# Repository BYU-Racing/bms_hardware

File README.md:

# BYU Racing 2027 BMS Project

This repo contains all relevant PCB files and explanations relating to the team's custom solution for a Battery Management System (BMS)

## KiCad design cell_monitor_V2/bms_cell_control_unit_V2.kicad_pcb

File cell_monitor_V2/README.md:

# BMS Cell Monitor V2 Files
This folder contains the KiCad project files for the BMS Cell Monitor V2.

PCB handoff from Rugby 11/10/2026 ☠️🌹⛓️

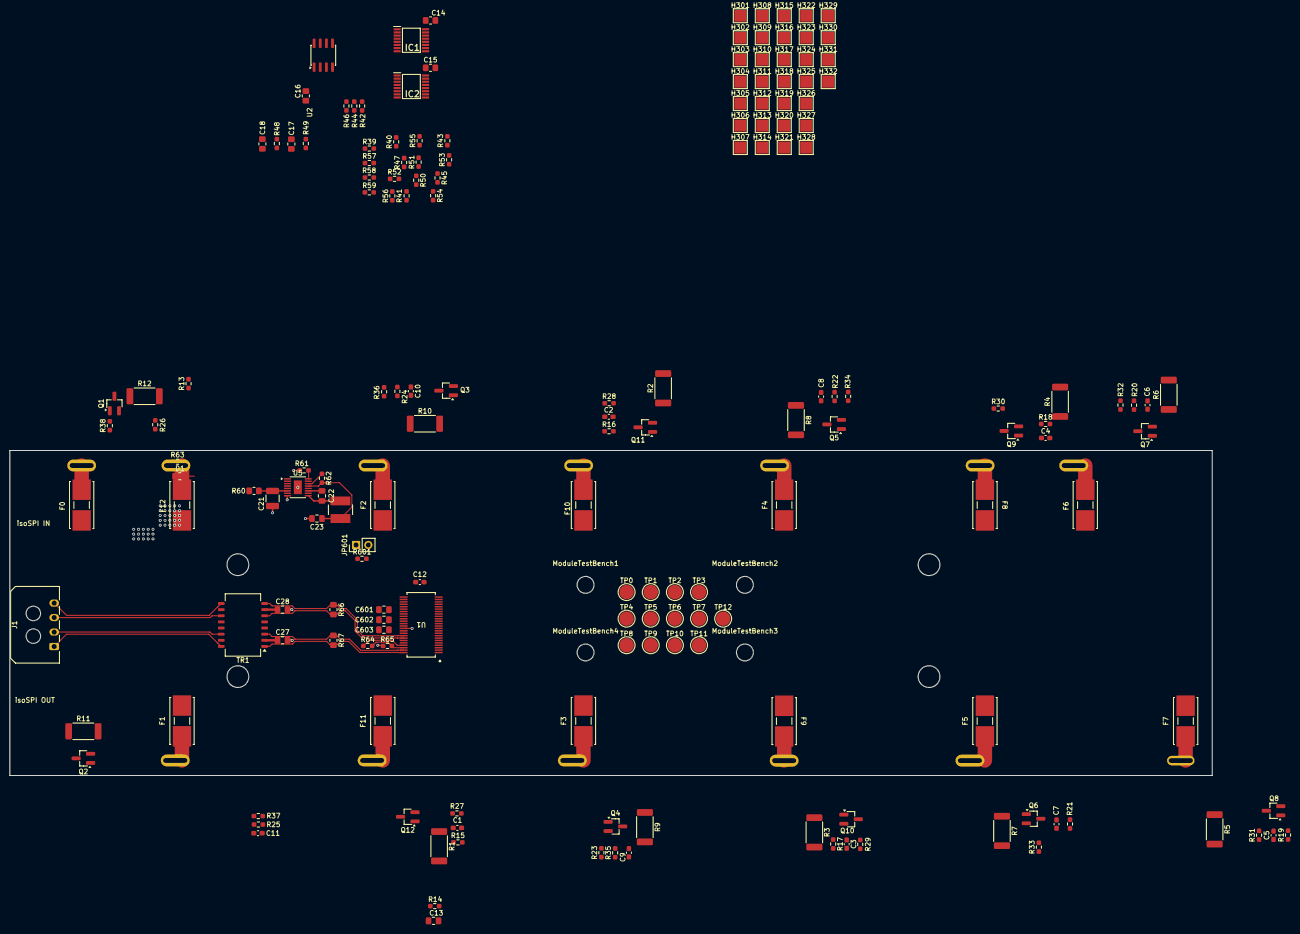
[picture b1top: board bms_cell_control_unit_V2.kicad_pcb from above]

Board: 4 copper layers, 249.0 x 67.3 mm, 199 parts (0 on the bottom side), 124 nets.

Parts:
C1, C2, C3, C4, C5, C6, C7, C8, C9, C10, C11, C12: 10nF; C_0603_1608Metric_Pad1.08x0.95mm_HandSolder
C13: 100nF; C_0805_2012Metric_Pad1.18x1.45mm_HandSolder
C14: 1uF; R_0805_2012Metric_Pad1.20x1.40mm_HandSolder
C15, C16: 1uf; R_0805_2012Metric_Pad1.20x1.40mm_HandSolder
C17, C18: 10nF; R_0805_2012Metric_Pad1.20x1.40mm_HandSolder
C21: 2.2uF; C_1210_3225Metric_Pad1.33x2.70mm_HandSolder
C22, C23: 22uF; C_0805_2012Metric_Pad1.18x1.45mm_HandSolder
C27, C28: 10nF; C_0805_2012Metric_Pad1.18x1.45mm_HandSolder
C601, C602, C603: 1uF; C_0805_2012Metric_Pad1.18x1.45mm_HandSolder
D1: LED; R_0805_2012Metric_Pad1.20x1.40mm_HandSolder
F0, F12: 500mA; Littelfuse_01550900M_Fuse_Blok_Cartridge
F1, F2, F3, F4, F5, F6, F7, F8, F9, F10, F11: 250mA; Littelfuse_01550900M_Fuse_Blok_Cartridge
H0, H1, H2, H3, H4, H5, H6, H7, H8, H9, H10, H11, H12: Old Voltage Tap; voltage_tap
H13, H14, H14#2, H14#3, H14#4, H14#5, H15, H16: MountingScrew; MountingHole_4mm
H301: TH1+; TestPoint_Pad_2.5x2.5mm
H302: TH2+; TestPoint_Pad_2.5x2.5mm
H303: TH1-; TestPoint_Pad_2.5x2.5mm
H304: TH2-; TestPoint_Pad_2.5x2.5mm
H305: TH3+; TestPoint_Pad_2.5x2.5mm
H306: TH4+; TestPoint_Pad_2.5x2.5mm
H307: TH4-; TestPoint_Pad_2.5x2.5mm
H308: TH3-; TestPoint_Pad_2.5x2.5mm
H309: TH5+; TestPoint_Pad_2.5x2.5mm
H310: TH6+; TestPoint_Pad_2.5x2.5mm
H311: TH6-; TestPoint_Pad_2.5x2.5mm
H312: TH5-; TestPoint_Pad_2.5x2.5mm
H313: TH7+; TestPoint_Pad_2.5x2.5mm
H314: TH8+; TestPoint_Pad_2.5x2.5mm
H315: TH8-; TestPoint_Pad_2.5x2.5mm
H316: TH7-; TestPoint_Pad_2.5x2.5mm
H317: TH9+; TestPoint_Pad_2.5x2.5mm
H318: TH10+; TestPoint_Pad_2.5x2.5mm
H319: TH10-; TestPoint_Pad_2.5x2.5mm
H320: TH9-; TestPoint_Pad_2.5x2.5mm
H321: TH11+; TestPoint_Pad_2.5x2.5mm
H322: TH12+; TestPoint_Pad_2.5x2.5mm
H323: TH12-; TestPoint_Pad_2.5x2.5mm
H324: TH11-; TestPoint_Pad_2.5x2.5mm
H325: TH13+; TestPoint_Pad_2.5x2.5mm
H326: TH14+; TestPoint_Pad_2.5x2.5mm
H327: TH15+; TestPoint_Pad_2.5x2.5mm
H328: TH16+; TestPoint_Pad_2.5x2.5mm
H329: TH14-; TestPoint_Pad_2.5x2.5mm
H330: TH16-; TestPoint_Pad_2.5x2.5mm
H331: TH13-; TestPoint_Pad_2.5x2.5mm
H332: TH15-; TestPoint_Pad_2.5x2.5mm
IC1, IC2: TMUX1308AQPWRQ1; SOP65P640X120-16N
J1: isoSPI Daisy Chain IN; Molex_Micro-Fit_3.0_43650-0400_1x04_P3.00mm_Horizontal
JP601: Current Jumper; PinHeader_1x02_P2.54mm_Vertical
L1: 33uH; IND_LQH5BPH330MT0L
ModuleTestBench1, ModuleTestBench2, ModuleTestBench3, ModuleTestBench4: MountingHole; MountingHole_3.5mm
Q1, Q2, Q3, Q4, Q5, Q6, Q7, Q8, Q9, Q10, Q11, Q12: BSS308PE; SOT-23_Handsoldering
R1, R2, R3, R4, R5, R6, R7, R8, R9, R10, R11, R12: 33; R_2512_6332Metric_Pad1.40x3.35mm_HandSolder
R13, R14, R15, R16, R17, R18, R19, R20, R21, R22, R23, R24, R25, R26, R48, R49: 100; R_0603_1608Metric_Pad0.98x0.95mm_HandSolder
R27, R28, R29, R30, R31, R32, R33, R34, R35, R36, R37, R38: 3.3k; R_0603_1608Metric_Pad0.98x0.95mm_HandSolder
R39, R40, R41, R43, R45, R47, R50, R51, R52, R53, R54, R55, R56, R57, R58, R59: 10k; R_0603_1608Metric_Pad0.98x0.95mm_HandSolder
R42, R44, R46: 4.7K; R_0603_1608Metric_Pad0.98x0.95mm_HandSolder
R60: 470; R_0805_2012Metric_Pad1.20x1.40mm_HandSolder
R61: 374k; R_0603_1608Metric_Pad0.98x0.95mm_HandSolder
R62: 220k; R_0603_1608Metric_Pad0.98x0.95mm_HandSolder
R63: 2.2k; R_0603_1608Metric_Pad0.98x0.95mm_HandSolder
R64, R65: 1k; R_0603_1608Metric_Pad0.98x0.95mm_HandSolder
R66, R67: 100; R_0805_2012Metric_Pad1.20x1.40mm_HandSolder
R601: 0; R_0603_1608Metric_Pad0.98x0.95mm_HandSolder
TP0, TP1, TP2, TP3, TP4, TP5, TP6, TP7, TP8, TP9, TP10, TP11, TP12: TestPoint; TestPoint_Pad_D3.0mm
TR1: TG110I-AE050N5xx; Transformer_Ethernet_Halo_N5_SO-16_7.11x12.7mm
U1: LTC6811HGI-1I-3ZZTRPBF; 05-08-1887_ADI
U2: TLV9002IDR; SOIC-8_3.9x4.9mm_P1.27mm
U5: LT3990HMSEI-5I-PBF; MSOP-16-1EP_3x4.039mm_P0.5mm_EP1.651x2.845mm

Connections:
/Power Rail/DRIVE: U1.38 (DRIVE), U5.4 (EN/UVLO)
/Power Rail/VREG: C14.1, C15.1, C16.1, C603.1, IC1.16 (VDD), IC2.16 (VDD), JP601.2 (B), R42.1, R44.1, R46.1, R63.2, R601.2, U1.37 (VREG), U1.40 (ISOMD), U2.8 (V+)
/Power Rail/V_REF1: C602.1, U1.35 (VREF1)
/Power Rail/V_REF2: C601.1, R39.1, R40.1, R41.1, R43.1, R45.1, R47.1, R50.1, R51.1, R52.1, R53.1, R54.1, R55.1, R56.1, R57.1, R58.1, R59.1, U1.34 (VREF2)
/Power Rail/V_full_stack_fused: F12.2, Q12.2 (S), R14.2, R15.2, R60.2, TP12.1 (1_1)
/Temperature Sensing/GPIO1(MUX_OUT_1): C18.1, R48.1, U1.27 (GPIO1)
/Temperature Sensing/GPIO2(MUX_OUT_2): C17.1, R49.1, U1.28 (GPIO2)
/Temperature Sensing/GPIO3: IC1.11 (A0), IC2.11 (A0), R42.2, U1.29 (GPIO3)
/Temperature Sensing/GPIO4: IC1.10 (A1), IC2.10 (A1), R44.2, U1.32 (GPIO4)
/Temperature Sensing/GPIO5: IC1.9 (A2), IC2.9 (A2), R46.2, U1.33 (GPIO5)
/Temperature Sensing/MUX1_OUT: IC1.3 (D), U2.3
/Temperature Sensing/MUX2_OUT: IC2.3 (D), U2.5
/Temperature Sensing/TH1: H301.1 (1_1), IC1.13 (S0), R39.2
/Temperature Sensing/TH2: H302.1 (1_1), IC1.14 (S1), R40.2
/Temperature Sensing/TH3: H305.1 (1_1), IC1.15 (S2), R41.2
/Temperature Sensing/TH4: H306.1 (1_1), IC1.12 (S3), R43.2
/Temperature Sensing/TH5: H309.1 (1_1), IC1.1 (S4), R45.2
/Temperature Sensing/TH6: H310.1 (1_1), IC1.5 (S5), R47.2
/Temperature Sensing/TH7: H313.1 (1_1), IC1.2 (S6), R50.2
/Temperature Sensing/TH8: H314.1 (1_1), IC1.4 (S7), R51.2
/Temperature Sensing/TH9: H317.1 (1_1), IC2.13 (S0), R52.2
/Temperature Sensing/TH10: H318.1 (1_1), IC2.14 (S1), R53.2
/Temperature Sensing/TH11: H321.1 (1_1), IC2.15 (S2), R54.2
/Temperature Sensing/TH12: H322.1 (1_1), IC2.12 (S3), R55.2
/Temperature Sensing/TH13: H325.1 (1_1), IC2.1 (S4), R56.2
/Temperature Sensing/TH14: H326.1 (1_1), IC2.5 (S5), R57.2
/Temperature Sensing/TH15: H327.1 (1_1), IC2.2 (S6), R58.2
/Temperature Sensing/TH16: H328.1 (1_1), IC2.4 (S7), R59.2
/Voltage Sense Leads/C0: C12.2, R13.1, U1.26 (C0)
/Voltage Sense Leads/C1: C11.2, C12.1, R26.1, U1.24 (C1)
/Voltage Sense Leads/C2: C10.2, C11.1, R25.1, U1.22 (C2)
/Voltage Sense Leads/C3: C9.2, C10.1, R24.1, U1.20 (C3)
/Voltage Sense Leads/C4: C8.2, C9.1, R23.1, U1.18 (C4)
/Voltage Sense Leads/C5: C7.2, C8.1, R22.1, U1.16 (C5)
/Voltage Sense Leads/C6: C6.2, C7.1, R21.1, U1.14 (C6)
/Voltage Sense Leads/C7: C5.2, C6.1, R20.1, U1.12 (C7)
/Voltage Sense Leads/C8: C4.2, C5.1, R19.1, U1.10 (C8)
/Voltage Sense Leads/C9: C3.2, C4.1, R18.1, U1.8 (C9)
/Voltage Sense Leads/C10: C2.2, C3.1, R17.1, U1.6 (C10)
/Voltage Sense Leads/C11: C1.2, C2.1, R16.1, U1.4 (C11)
/Voltage Sense Leads/C12: C1.1, R15.1, U1.2 (C12)
/Voltage Sense Leads/S1: R38.1, U1.25 (S1)
/Voltage Sense Leads/S2: R37.1, U1.23 (S2)
/Voltage Sense Leads/S3: R36.1, U1.21 (S3)
/Voltage Sense Leads/S4: R35.1, U1.19 (S4)
/Voltage Sense Leads/S5: R34.1, U1.17 (S5)
/Voltage Sense Leads/S6: R33.1, U1.15 (S6)
/Voltage Sense Leads/S7: R32.1, U1.13 (S7)
/Voltage Sense Leads/S8: R31.1, U1.11 (S8)
/Voltage Sense Leads/S9: R30.1, U1.9 (S9)
/Voltage Sense Leads/S10: R29.1, U1.7 (S10)
/Voltage Sense Leads/S11: R28.1, U1.5 (S11)
/Voltage Sense Leads/S12: R27.1, U1.3 (S12)
/Voltage Sense Leads/VBUS1: F1.1, H1.1 (1_1)
/Voltage Sense Leads/VBUS2: F2.1, H2.1 (1_1)
/Voltage Sense Leads/VBUS3: F3.1, H3.1 (1_1)
/Voltage Sense Leads/VBUS4: F4.1, H4.1 (1_1)
/Voltage Sense Leads/VBUS5: F5.1, H5.1 (1_1)
/Voltage Sense Leads/VBUS6: F6.1, H6.1 (1_1)
/Voltage Sense Leads/VBUS7: F7.1, H7.1 (1_1)
/Voltage Sense Leads/VBUS8: F8.1, H8.1 (1_1)
/Voltage Sense Leads/VBUS9: F9.1, H9.1 (1_1)
/Voltage Sense Leads/VBUS10: F10.1, H10.1 (1_1)
/Voltage Sense Leads/VBUS11: F11.1, H11.1 (1_1)
/Voltage Sense Leads/VBUS12: F12.1, H12.1 (1_1)
/Voltage Sense Leads/VBUS_GNDREF: F0.1, H0.1 (1_1)
/Voltage Sense Leads/VI+: C13.1, R14.1, U1.1 (V+)
/isoSPI Daisy Chain/+: R66.2, TR1.6 (RX-), U1.42 (SCK(IPA))
/isoSPI Daisy Chain/-: R66.1, TR1.8 (RX+), U1.41 (CSB(IMA))
/isoSPI Daisy Chain/I+: R67.2, TR1.1 (TX-), U1.48 (IPB)
/isoSPI Daisy Chain/I-: R67.1, TR1.3 (TX+), U1.47 (IMB)
/isoSPI Daisy Chain/IBIAS: R64.2, U1.45 (IBIAS)
/isoSPI Daisy Chain/ICMP: R64.1, R65.2, U1.46 (ICMP)
/isoSPI Daisy Chain/isoSPIAI+: J1.3, TR1.11 (RD-)
/isoSPI Daisy Chain/isoSPIAI-: J1.4, TR1.9 (RD+)
/isoSPI Daisy Chain/isoSPIBI+: J1.1, TR1.16 (TD-)
/isoSPI Daisy Chain/isoSPIBI-: J1.2, TR1.14 (TD+)
GNDREF: C13.2, C14.2, C15.2, C16.2, C17.2, C18.2, C21.2, C23.2, C27.2, C28.2, C601.2, C602.2, C603.2, D1.1 (K), F0.2, H303.1 (1_1), H304.1 (1_1), H307.1 (1_1), H308.1 (1_1), H311.1 (1_1), H312.1 (1_1), H315.1 (1_1), H316.1 (1_1), H319.1 (1_1), H320.1 (1_1), H323.1 (1_1), H324.1 (1_1), H329.1 (1_1), H330.1 (1_1), H331.1 (1_1), H332.1 (1_1), IC1.6 (~EN), IC1.8 (GND), IC2.6 (~EN), IC2.8 (GND), R12.2, R13.2, R61.2, R65.1, TP0.1 (1_1), U1.30 (V-), U1.31 (V-), U1.36 (DTEN), U2.4 (V-), U5.8 (GND), U5.17 (EPAD)
unnamed: D1.2 (A), R63.1
unnamed: C23.1, JP601.1 (A), L1.2, R62.1, R601.1, U5.1 (FB/VOUT), U5.2 (FB/VOUT), U5.13 (BD)
unnamed: Q1.3 (D), R12.1
unnamed: Q1.1 (G), R38.2
unnamed: F1.2, Q1.2 (S), R11.2, R26.2, TP1.1 (1_1)
unnamed: Q2.3 (D), R11.1
unnamed: Q2.1 (G), R37.2
unnamed: F2.2, Q2.2 (S), R10.2, R25.2, TP2.1 (1_1)
unnamed: Q3.3 (D), R10.1
unnamed: Q3.1 (G), R36.2
unnamed: F3.2, Q3.2 (S), R9.2, R24.2, TP3.1 (1_1)
unnamed: Q4.3 (D), R9.1
unnamed: Q4.1 (G), R35.2
unnamed: F4.2, Q4.2 (S), R8.2, R23.2, TP4.1 (1_1)
unnamed: Q5.3 (D), R8.1
unnamed: Q5.1 (G), R34.2
unnamed: F5.2, Q5.2 (S), R7.2, R22.2, TP5.1 (1_1)
unnamed: Q6.3 (D), R7.1
unnamed: Q6.1 (G), R33.2
unnamed: F6.2, Q6.2 (S), R6.2, R21.2, TP6.1 (1_1)
unnamed: Q7.3 (D), R6.1
unnamed: Q7.1 (G), R32.2
unnamed: F7.2, Q7.2 (S), R5.2, R20.2, TP7.1 (1_1)
unnamed: Q8.3 (D), R5.1
unnamed: Q8.1 (G), R31.2
unnamed: F8.2, Q8.2 (S), R4.2, R19.2, TP8.1 (1_1)
unnamed: Q9.3 (D), R4.1
unnamed: Q9.1 (G), R30.2
unnamed: F9.2, Q9.2 (S), R3.2, R18.2, TP9.1 (1_1)
unnamed: Q10.3 (D), R3.1
unnamed: Q10.1 (G), R29.2
unnamed: F10.2, Q10.2 (S), R2.2, R17.2, TP10.1 (1_1)
unnamed: Q11.3 (D), R2.1
unnamed: Q11.1 (G), R28.2
unnamed: F11.2, Q11.2 (S), R1.2, R16.2, TP11.1 (1_1)
unnamed: Q12.3 (D), R1.1
unnamed: Q12.1 (G), R27.2
unnamed: R48.2, U2.1, U2.2
unnamed: R49.2, U2.6, U2.7
unnamed: C28.1, TR1.7 (C_RX)
unnamed: C27.1, TR1.2 (C_TX)
unnamed: C22.1, U5.11 (BOOST)
unnamed: R62.2, U5.14 (PG)
unnamed: R61.1, U5.16 (RT)
unnamed: C22.2, L1.1, U5.9 (SW)
unnamed: C21.1, R60.1, U5.6 (VIN)

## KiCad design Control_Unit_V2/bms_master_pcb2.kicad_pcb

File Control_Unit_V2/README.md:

# BMS Control Unit V2 Files
This folder contains the KiCad project files for the BMS Control Unit V2.

PCB handoff from Rugby 11/10/2026 ☠️🌹⛓️

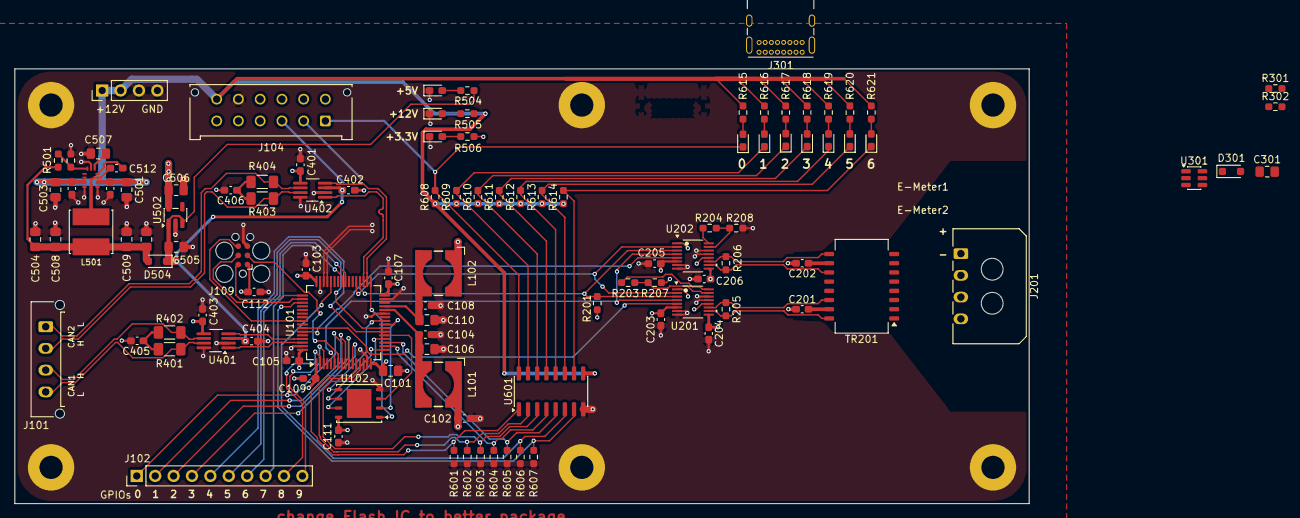
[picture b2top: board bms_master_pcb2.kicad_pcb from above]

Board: 4 copper layers, 140.0 x 60.0 mm, 115 parts (0 on the bottom side), 91 nets.

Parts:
C101: 4.7u; C_0805_2012Metric_Pad1.18x1.45mm_HandSolder
C102, C103, C104, C105, C107, C108, C109, C111, C112, C203, C204, C205, C206, C401, C402, C403, C404: 100n; C_0603_1608Metric_Pad1.08x0.95mm_HandSolder
C106, C110, C505, C506, C507: 1u; C_0805_2012Metric_Pad1.18x1.45mm_HandSolder
C201, C202: 27p; C_0603_1608Metric_Pad1.08x0.95mm_HandSolder
C301, C501, C503: 10u; C_0805_2012Metric_Pad1.18x1.45mm_HandSolder
C405, C406: 240p; C_0603_1608Metric_Pad1.08x0.95mm_HandSolder
C502, C504, C508, C509: 22u; C_0805_2012Metric_Pad1.18x1.45mm_HandSolder
C510, C511: 220n; C_0603_1608Metric_Pad1.08x0.95mm_HandSolder
C512: 0.1u; C_0603_1608Metric_Pad1.08x0.95mm_HandSolder
D301, D504: 1N4448WS; D_SOD-323_HandSoldering
D501: 5V LED; LED_0603_1608Metric_Pad1.05x0.95mm_HandSolder
D502: 12V LED; LED_0603_1608Metric_Pad1.05x0.95mm_HandSolder
D503: 3.3V LED; LED_0603_1608Metric_Pad1.05x0.95mm_HandSolder
D601, D602, D603, D604, D605, D606, D607: LED_Small; LED_0603_1608Metric_Pad1.05x0.95mm_HandSolder
H101, H102, H103, H104, H105, H106: MountingHole; MountingHole_3.2mm_M3_Pad
J101: CAN Connector; Molex_Micro-Fit_3.0_43650-0415_1x04_P3.00mm_Vertical
J102: GPIO; PinHeader_1x10_P2.54mm_Vertical
J103: EXTRA POWER IN; PinHeader_1x04_P2.54mm_Vertical
J104: Connector to GLV plug; Molex_Micro-Fit_3.0_43045-1212_2x06_P3.00mm_Vertical
J109: TC2030; Tag-Connect_TC2030-IDC-FP_2x03_P1.27mm_Vertical
J201: isoSPI Daisy Chain; Molex_Micro-Fit_3.0_43650-0400_1x04_P3.00mm_Horizontal
J301: USB4085-GF-A; USB_C_Receptacle_GCT_USB4085
L101, L102: 100u; WE-HEPC_6030
L501: 10u; IND_SRN6045TA-2R2Y
R201: 2K; R_0603_1608Metric_Pad0.98x0.95mm_HandSolder
R203, R204, R207, R208, R506: 1k; R_0603_1608Metric_Pad0.98x0.95mm_HandSolder
R205, R206: 100; R_0603_1608Metric_Pad0.98x0.95mm_HandSolder
R301, R302: 5.1K; R_0603_1608Metric_Pad0.98x0.95mm_HandSolder
R401, R402, R403, R404: 60; R_1206_3216Metric_Pad1.30x1.75mm_HandSolder
R501: 100k; R_0603_1608Metric_Pad0.98x0.95mm_HandSolder
R502: 24.9k; R_0603_1608Metric_Pad0.98x0.95mm_HandSolder
R504: 2.2k; R_0603_1608Metric_Pad0.98x0.95mm_HandSolder
R505, R615, R616, R617, R618, R619, R620, R621: 4.7k; R_0603_1608Metric_Pad0.98x0.95mm_HandSolder
R601, R602, R603, R604, R605, R606, R607, R608, R609, R610, R611, R612, R613, R614: 10K; R_0603_1608Metric_Pad0.98x0.95mm_HandSolder
TR201: TG110-E050N5xx; Transformer_Ethernet_Halo_N5_SO-16_7.11x12.7mm
U101: STM32G474RETx; LQFP-64_10x10mm_P0.5mm
U102: SST26VF064B-104V/MF; WDFN-8-1EP_6x5mm_P1.27mm_EP3.4x4mm
U201, U202: LTC6820HMS-TRPBF; MS_05-08-1669_ADI
U301: USBLC6-2SC6; SOT-23-6
U401, U402: TCAN1044AVDDFRQ1; TSOT-23-8_HandSoldering
U502: AP2112K-3.3; SOT-23-5
U503: LMR33620CQ5RNXRQ1; RNX0012B
U601: TPL7407LAD; SOIC-16_3.9x9.9mm_P1.27mm

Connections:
+3.3V: C101.1, C102.1, C103.1, C105.1, C107.1, C109.1, C111.1, C112.1, C203.1, C204.1, C205.1, C206.1, C401.1, C403.1, C506.1, J109.1, L101.1, L102.1, R201.2, R506.1, U101.1 (VBAT), U101.16 (VDD), U101.32 (VDD), U101.48 (VDD), U101.64 (VDD), U102.8 (VCC), U201.1 (EN), U201.6 (VDDS), U201.9 (VDD), U201.12 (MSTR), U202.1 (EN), U202.6 (VDDS), U202.9 (VDD), U202.12 (MSTR), U401.5 (VIO), U402.5 (VIO), U502.5 (VOUT)
+5V: C301.1, C402.1, C404.1, C505.1, D301.1 (K), D504.1 (K), R504.1, U301.5 (VBUS), U401.3 (VCC), U402.3 (VCC), U502.1 (VIN), U502.3 (EN)
+12V: C501.1, C503.1, C510.2, C511.2, J103.1, J103.2, J104.12, R505.1, R608.1, R609.1, R610.1, R611.1, R612.1, R613.1, R614.1, R615.1, R616.1, R617.1, R618.1, R619.1, R620.1, R621.1, U503.2 (VIN), U503.9 (EN), U503.10 (VIN), U601.9 (COM)
/BMS SD STATUS: D601.1 (K), J104.1, R608.2, U601.16 (OUT1)
/CAN1_N: U101.62 (FDCAN1_TX), U401.1 (TXD)
/CAN1_P: U101.61 (FDCAN1_RX), U401.4 (RXD)
/CAN2_N: U101.35 (FDCAN2_TX), U402.1 (TXD)
/CAN2_P: U101.34 (FDCAN2_RX), U402.4 (RXD)
/CAN/CAN.1+: J101.4, R401.1, U401.7 (CANH)
/CAN/CAN.1-: J101.3, R402.1, U401.6 (CANL)
/CAN/CAN.2+: J101.2, R403.1, U402.7 (CANH)
/CAN/CAN.2-: J101.1, R404.1, U402.6 (CANL)
/DIG_OUT_0: R601.1, U101.12 (PA0), U601.1 (IN1)
/DIG_OUT_1: R602.1, U101.13 (PA1), U601.2 (IN2)
/DIG_OUT_2: R603.1, U101.14 (PA2), U601.3 (IN3)
/DIG_OUT_3: R604.1, U101.18 (PA4), U601.4 (IN4)
/DIG_OUT_4: R605.1, U101.19 (PA5), U601.5 (IN5)
/DIG_OUT_5: R606.1, U101.44 (PA10), U601.6 (IN6)
/DIG_OUT_6: R607.1, U101.51 (PA15), U601.7 (IN7)
/Digital Outputs and Happy Lights/BMS_OUT_1: D602.1 (K), R609.2, U601.15 (OUT2)
/Digital Outputs and Happy Lights/BMS_OUT_2: D603.1 (K), R610.2, U601.14 (OUT3)
/Digital Outputs and Happy Lights/BMS_OUT_3: D604.1 (K), R611.2, U601.13 (OUT4)
/Digital Outputs and Happy Lights/BMS_OUT_4: D605.1 (K), R612.2, U601.12 (OUT5)
/Digital Outputs and Happy Lights/BMS_OUT_5: D606.1 (K), R613.2, U601.11 (OUT6)
/Digital Outputs and Happy Lights/BMS_OUT_6: D607.1 (K), R614.2, U601.10 (OUT7)
/GPIO_0: J102.1, U101.8 (PC0)
/GPIO_1: J102.2, U101.9 (PC1)
/GPIO_2: J102.3, U101.10 (PC2)
/GPIO_3: J102.4, U101.11 (PC3)
/GPIO_4: J102.5, U101.22 (PC4)
/GPIO_5: J102.6, U101.23 (PC5)
/GPIO_6: J102.7, U101.40 (PC8)
/GPIO_7: J102.8, U101.41 (PC9)
/GPIO_8: J102.9, U101.2 (PC13)
/GPIO_9: J102.10, U101.3 (PC14)
/QSPI.CLK: U101.17 (QUADSPI1_CLK), U102.6 (SCK)
/QSPI.IO0: U101.25 (QUADSPI1_BK1_IO0), U102.5 (IO0)
/QSPI.IO1: U101.24 (QUADSPI1_BK1_IO1), U102.2 (IO1)
/QSPI.IO2: U101.21 (QUADSPI1_BK1_IO2), U102.3 (IO2)
/QSPI.IO3: U101.20 (QUADSPI1_BK1_IO3), U102.7 (IO3)
/QSPI.NCS: U101.33 (QUADSPI1_BK1_NCS), U102.1 (CE#)
/RESET: J109.3, U101.7 (RCC_MCO)
/SPI_CS1: U101.58 (PB5), U201.5 (*CS)
/SPI_CS2: U101.59 (PB6), U202.5 (*CS)
/SWCLK: J109.4, U101.50 (SYS_JTCK-SWCLK)
/SWDIO: J109.2, U101.49 (SYS_JTMS-SWDIO)
/SWO: J109.6, U101.56 (SYS_JTDO-SWO)
/USB/D+: J301.A6 (D+), J301.B6 (D+), U301.4 (I/O2)
/USB/D-: J301.A7 (D-), J301.B7 (D-), U301.6 (I/O1)
/USB/USB.D+: U101.46 (USB_DP), U301.3 (I/O2)
/USB/USB.D-: U101.45 (USB_DM), U301.1 (I/O1)
/isoSPI/INPUT_isoSPI.D+: J201.3, TR201.3 (TX-)
/isoSPI/INPUT_isoSPI.D-: J201.4, TR201.1
/isoSPI/OUTPUT_isoSPI.D+: J201.1, TR201.8 (RX-)
/isoSPI/OUTPUT_isoSPI.D-: J201.2, TR201.6 (RX+)
/isoSPI/SPI2.MISO: R201.1, U101.36 (SPI2_MISO), U201.3 (MISO), U202.3 (MISO)
/isoSPI/SPI2.MOSI: U101.37 (SPI2_MOSI), U201.2 (MOSI), U202.2 (MOSI)
/isoSPI/SPI2.SCK: U101.6 (SPI2_SCK), U201.4 (SCK), U202.4 (SCK)
/isoSPI/isoSPI.D+: R205.2, TR201.14 (TD-), U201.11 (IP)
/isoSPI/isoSPI.D-: R205.1, TR201.16 (TD+), U201.10 (IM)
/isoSPI/isoSPI_2.D+: R206.2, TR201.9 (RD-), U202.11 (IP)
/isoSPI/isoSPI_2.D-: R206.1, TR201.11 (RD+), U202.10 (IM)
GND: C101.2, C102.2, C103.2, C104.2, C105.2, C106.2, C107.2, C108.2, C109.2, C110.2, C111.2, C112.2, C201.2, C202.2, C203.2, C204.2, C205.2, C206.2, C301.2, C401.2, C402.2, C403.2, C404.2, C405.2, C406.2, C501.2, C502.2, C503.2, C504.2, C505.2, C506.2, C507.2, C508.2, C509.2, C510.1, C511.1, D501.1 (K), D502.1 (K), D503.1 (K), H101.1 (1_1), H102.1 (1_1), H103.1 (1_1), H104.1 (1_1), H105.1 (1_1), H106.1 (1_1), J103.3, J103.4, J104.11, J109.5, J301.A1 (GND), J301.A12 (GND), J301.B1 (GND), J301.B12 (GND), J301.SH (SHIELD), R207.2, R208.2, R301.2, R302.2, R502.1, R601.2, R602.2, R603.2, R604.2, R605.2, R606.2, R607.2, U101.15 (VSS), U101.27 (VSSA), U101.31 (VSS), U101.47 (VSS), U101.63 (VSS), U102.4 (VSS), U201.7 (POL), U201.8 (PHA), U201.13 (SLOW), U201.14 (GND), U202.7 (POL), U202.8 (PHA), U202.13 (SLOW), U202.14 (GND), U301.2 (GND), U401.2 (GND), U401.8 (STB), U402.2 (GND), U402.8 (STB), U502.2 (GND), U503.1 (PGND), U503.6 (AGND), U503.11 (PGND), U601.8 (GND)
unnamed: C405.1, R401.2, R402.2
unnamed: C406.1, R403.2, R404.2
unnamed: D301.2 (A), J301.A4 (VBUS), J301.A9 (VBUS), J301.B4 (VBUS), J301.B9 (VBUS)
unnamed: D501.2 (A), R504.2
unnamed: D502.2 (A), R505.2
unnamed: D503.2 (A), R506.2
unnamed: C502.1, C504.1, C508.1, C509.1, D504.2 (A), L501.2, R501.2
unnamed: D601.2 (A), R615.2
unnamed: D602.2 (A), R616.2
unnamed: D603.2 (A), R617.2
unnamed: D604.2 (A), R618.2
unnamed: D605.2 (A), R619.2
unnamed: D606.2 (A), R620.2
unnamed: D607.2 (A), R621.2
unnamed: J301.A5 (CC1), R301.1
unnamed: J301.B5 (CC2), R302.1
unnamed: C202.1, TR201.10 (C_RD)
unnamed: C201.1, TR201.15 (C_TD)
unnamed: C108.1, C110.1, L102.2, U101.29 (VDDA)
unnamed: C104.1, C106.1, L101.2, U101.28 (VREF+)
unnamed: R203.1, U201.16 (IBIAS)
unnamed: R203.2, R207.1, U201.15 (ICMP)
unnamed: R204.1, U202.16 (IBIAS)
unnamed: R204.2, R208.1, U202.15 (ICMP)
unnamed: C512.2, U503.4 (BOOT)
unnamed: R501.1, R502.2, U503.7 (FB)
unnamed: C512.1, L501.1, U503.3 (NC), U503.12 (SW)
unnamed: C507.1, U503.5 (VCC)

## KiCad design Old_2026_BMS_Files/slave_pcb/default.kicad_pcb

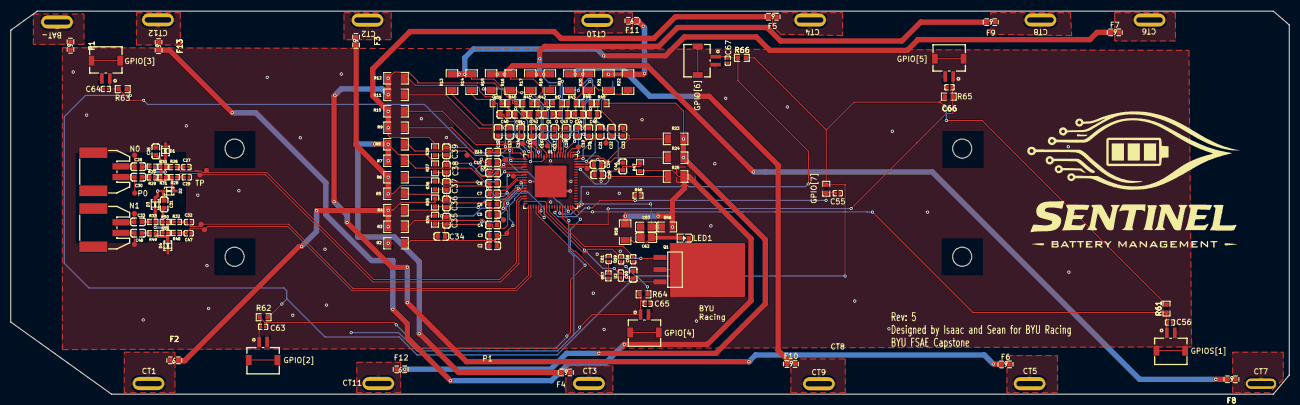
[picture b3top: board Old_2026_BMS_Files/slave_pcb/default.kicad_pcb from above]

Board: 2 copper layers, 241.0 x 72.2 mm, 184 parts (0 on the bottom side), 98 nets.

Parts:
C1, C34, C35, C36, C37, C38, C39, C40, C41, C42, C43, C44, C45, C46: 10nF ±10% 50V X7R; C0603
C2, C3, C4, C5, C6, C7, C8, C9, C10, C11, C12, C13, C14, C15, C16, C17, C18, C19, C20, C21, C22, C23, C24, C25, C26, C31: 100nF ±10% 50V X7R; C0603
C27, C29, C32, C47: 330pF ±10% 50V X7R; C0402
C28, C30, C33, C48: 22nF ±10% 50V X7R; C0603
C55, C56, C63, C64, C65, C66, C67: 100nF ±10% 16V X7R; C0402
C57: 10nF ±10% 50V X7R; C0805
C58, C59: 1µF ±10% 25V X5R; C0402
C60: 1µF ±10% 50V X5R; C0603
C61: 10nF ±10% 50V X7R; C0402
C62: 10nF ±10% 100V X7R; C0805
CN1, CN2: CONN-SMD-2P_5023520200
CN3, CN4, CN5, CN6, CN7, CN8: CONN-SMD_S2B-ZR-SM4A
D1, D2, D3, D4: SOD-323_L1.8-W1.3-LS2.5-BI
F1, F2, F3, F4, F5, F6, F7, F8, F9, F10, F11, F12, F13: F0603
LED1: LED0603-RD
Q1: SOT-223-4_L6.5-W3.5-P2.30-LS7.0-BR
R1, R34, R35, R36, R37, R38, R39, R40, R41, R42, R43, R44, R45, R47: 200Ω ±1% 100mW; R0603
R2, R3, R4, R5, R6, R7, R8, R9, R10, R11, R12, R13, R14, R15, R16, R17, R18, R19, R20, R21, R22, R23, R24, R25: 22Ω ±1% 250mW; R1206
R26, R28, R32, R48: 22Ω ±1% 62.5mW; R0402
R27, R29, R33, R49: 15Ω ±1% 62.5mW; R0402
R30, R31, R50, R51: 43Ω ±1% 62.5mW; R0402
R46: R0402
R56: 1kΩ ±1% 125mW; R0805
R57: 10Ω ±1% 62.5mW; R0402
R58: 330Ω ±5% 250mW; R1206
R60, R61, R62, R63, R64, R65, R66: 10kΩ ±1% 100mW; R0603
TP1, TP2, TP3, TP4, TP5, TP6, TP7, TP8, TP9, TP10, TP11, TP12, TP13: voltage_tap
TP14, TP15, TP16, TP17, TP18, TP19, TP20, TP21, TP22, TP23, TP24, TP25, TP26, TP27, TP28, TP29, TP30, TP31, TP32, TP33: TestPoint_Pad_D1.0mm
U1: QFN-72_L10.0-W10.0-P0.50-BL-EP6.0_1
U2: L0402

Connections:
A: C62.1, LED1.2, R58.2
C0: C34.1, C35.2, R34.2, U1.50
C1: C35.1, C36.2, R35.2, U1.48
C2: C36.1, C37.2, R36.2, U1.45
C3: C37.1, C38.2, R37.2, U1.42
C4: C38.1, C39.2, R38.2, U1.39
C5: C39.1, C40.2, R39.2, U1.36
C6: C40.1, C41.2, R40.2, U1.33
C7: C41.1, C42.2, R41.2, U1.30
C8: C1.2, C42.1, R42.2, U1.27
C9: C43.1, C44.2, R43.2, U1.23
C9N: C1.1, C43.2, R1.2, U1.26
C10: C44.1, C45.2, R44.2, U1.20
C11: C45.1, C46.2, R45.2, U1.17
C12: C46.1, R47.2, U1.14
DRIVE: R57.1, U1.58
K: LED1.1, Q1.2, Q1.4
S1N: C2.1, C3.2, R2.2, TP22.1, U1.59
S1P: C3.1, C4.2, R3.2, U1.49
S2N: C4.1, C5.2, R4.2, TP23.1, U1.46
S2P: C5.1, C6.2, R5.2, U1.47
S3N: C6.1, C7.2, R6.2, TP24.1, U1.43
S3P: C7.1, C8.2, R7.2, U1.44
S4N: C8.1, C9.2, R8.2, TP25.1, U1.40
S4P: C9.1, C10.2, R9.2, U1.41
S5N: C10.1, C11.2, R10.2, TP26.1, U1.37
S5P: C11.1, C12.2, R11.2, U1.38
S6N: C12.1, C13.2, R12.2, TP27.1, U1.34
S6P: C13.1, C14.2, R13.2, U1.35
S7N: C14.1, C15.2, R14.2, TP28.1, U1.31
S7P: C15.1, C16.2, R15.2, U1.32
S8N: C16.1, C17.2, R16.2, TP29.1, U1.28
S8P: C17.1, C18.2, R17.2, U1.29
S9N: C18.1, C19.2, R18.2, TP30.1, U1.24
S9P: C19.1, C20.2, R19.2, U1.25
S10N: C20.1, C21.2, R20.2, TP31.1, U1.21
S10P: C21.1, C22.2, R21.2, U1.22
S11N: C22.1, C23.2, R22.2, TP32.1, U1.18
S11P: C23.1, C24.2, R23.2, U1.19
S12N: C24.1, C25.2, R24.2, TP33.1, U1.15
S12P: C25.1, R25.2, U1.16
asic_vp-VCC: C57.1, R56.2, U1.1
base: C61.1, Q1.1, R57.2
bat-: C2.2, C26.2, C27.2, C29.2, C31.2, C32.2, C34.2, C47.2, C55.2, C56.2, C57.2, C58.2, C59.2, C60.2, C61.2, C62.2, C63.2, C64.2, C65.2, C66.2, C67.2, CN3.2, CN4.2, CN5.2, CN6.2, CN7.2, CN8.2, D1.1, D2.1, D3.1, D4.1, F1.2, R2.1, R34.1, R46.2, U1.60, U1.73
cell_tap_1: F2.2, R3.1, R4.1, R35.1
cell_tap_2: F3.2, R5.1, R6.1, R36.1
cell_tap_3: F4.2, R7.1, R8.1, R37.1
cell_tap_4: F5.2, R9.1, R10.1, R38.1
cell_tap_5: F6.2, R11.1, R12.1, R39.1
cell_tap_6: F7.2, R13.1, R14.1, R40.1
cell_tap_7: F8.2, R15.1, R16.1, R41.1
cell_tap_8: F9.2, R1.1, R17.1, R18.1, R42.1
cell_tap_9: F10.2, R19.1, R20.1, R43.1
cell_tap_10: F11.2, R21.1, R22.1, R44.1
cell_tap_11: F12.2, R23.1, R24.1, R45.1
cell_tap_12: F13.2, R25.1, R47.1, R56.1, R58.1
cell_tap_fuses[0]-_1: F1.1, TP1.1
cell_tap_fuses[1]-_1: F2.1, TP2.1
cell_tap_fuses[2]-_1: F3.1, TP3.1
cell_tap_fuses[3]-_1: F4.1, TP4.1
cell_tap_fuses[4]-_1: F5.1, TP5.1
cell_tap_fuses[5]-_1: F6.1, TP6.1
cell_tap_fuses[6]-_1: F7.1, TP7.1
cell_tap_fuses[7]-_1: F8.1, TP8.1
cell_tap_fuses[8]-_1: F9.1, TP9.1
cell_tap_fuses[9]-_1: F10.1, TP10.1
cell_tap_fuses[10]-_1: F11.1, TP11.1
cell_tap_fuses[11]-_1: F12.1, TP12.1
cell_tap_fuses[12]-_1: F13.1, TP13.1
common_mode_cap-common_mode_node-0: C26.1, R30.2, R31.2
common_mode_cap-common_mode_node-1: C31.1, R50.2, R51.2
damping_resistor-point_a-0: D1.2, R26.2, R27.1, R30.1
damping_resistor-point_a-1: D2.2, R28.2, R29.1, R31.1
damping_resistor-point_a-2: D3.2, R32.2, R33.1, R50.1
damping_resistor-point_a-3: D4.2, R48.2, R49.1, R51.1
emitter: Q1.3, U2.1
footprint-net-0: C28.1, R27.2
footprint-net-1: C30.1, R29.2
footprint-net-2: C33.1, R33.2
footprint-net-3: C48.1, R49.2
gpios[0]-output_signal: C56.1, CN3.1, R61.2, U1.72
gpios[1]-output_signal: C63.1, CN4.1, R62.2, U1.71
gpios[2]-output_signal: C64.1, CN5.1, R63.2, U1.70
gpios[3]-output_signal: C65.1, CN6.1, R64.2, U1.69
gpios[4]-output_signal: C66.1, CN7.1, R65.2, U1.68
gpios[5]-output_signal: C67.1, CN8.1, R66.2, U1.67
gpios[6]-output_signal: C55.1, R46.1, R60.2, U1.66
isoA_N: C27.1, R26.1, TP15.1, U1.51
isoA_P: C29.1, R28.1, TP17.1, U1.52
isoB_N: C32.1, R32.1, TP19.1, U1.55
isoB_P: C47.1, R48.1, TP21.1, U1.56
isoSPI_filters[0]-output_pair-contact_N: C28.2, CN1.2, TP14.1
isoSPI_filters[0]-output_pair-contact_P: C30.2, CN1.1, TP16.1
isoSPI_filters[1]-output_pair-contact_N: C33.2, CN2.2, TP18.1
isoSPI_filters[1]-output_pair-contact_P: C48.2, CN2.1, TP20.1
vref1-VCC: C58.1, U1.63
vref2-VCC: C59.1, R60.1, R61.1, R62.1, R63.1, R64.1, R65.1, R66.1, U1.61
vreg-VCC: C60.1, U1.53, U1.62, U2.2
